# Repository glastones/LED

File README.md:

# LED
LED SPOT (First Try in Kicad)

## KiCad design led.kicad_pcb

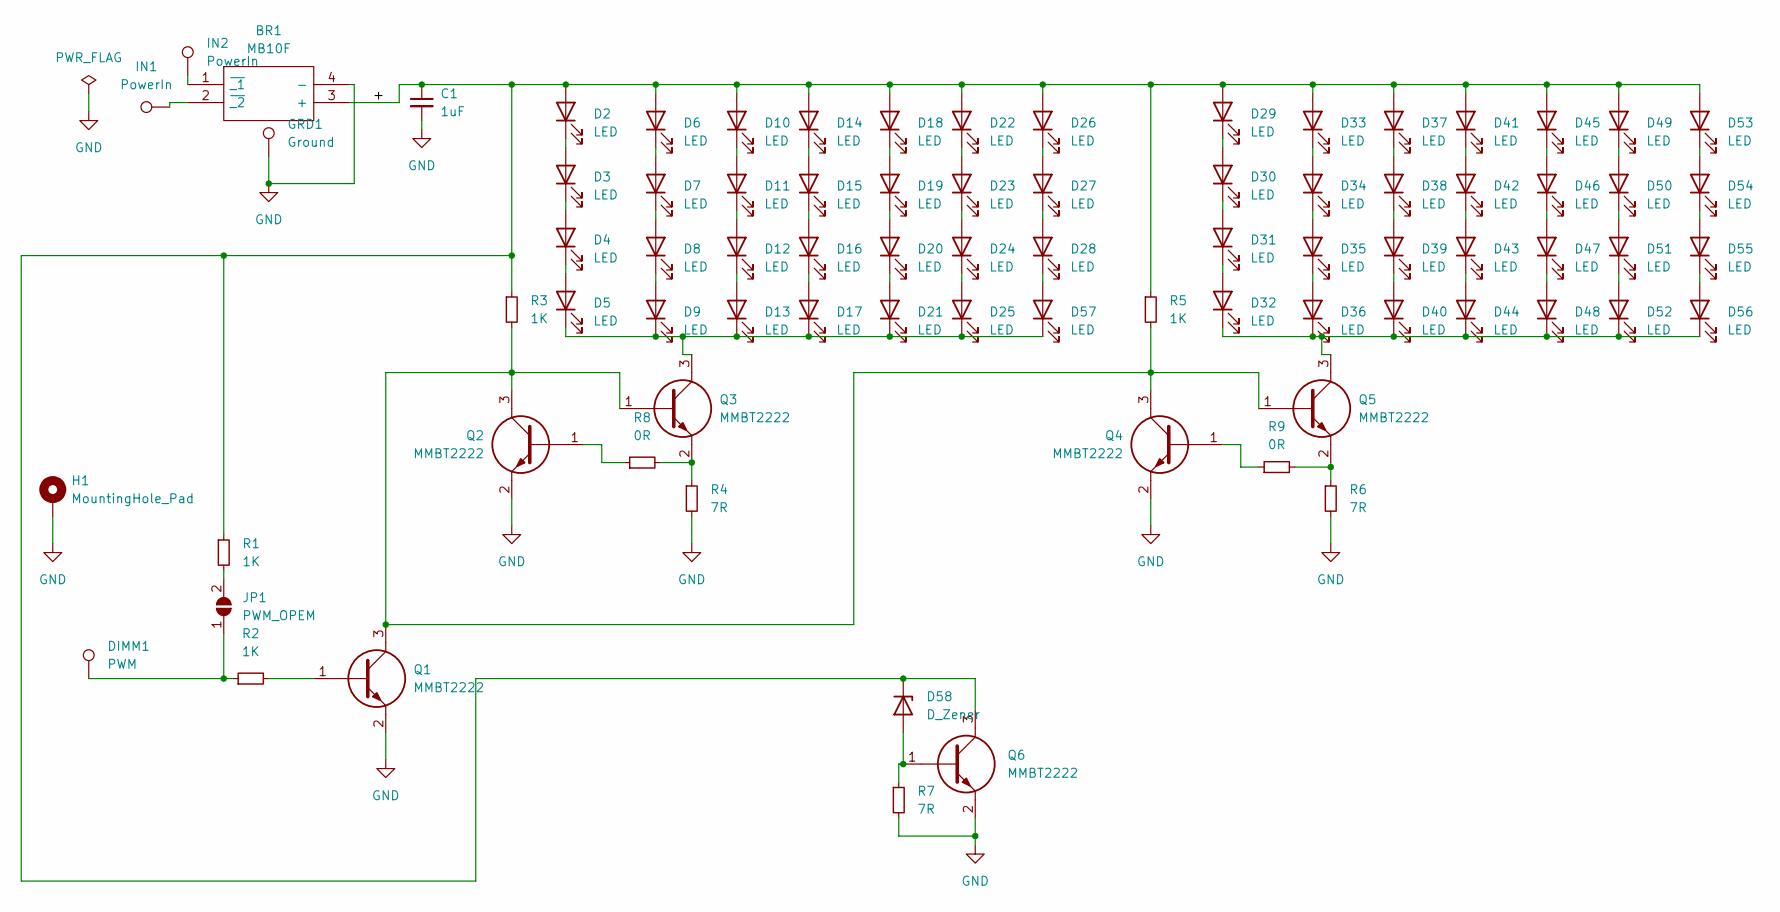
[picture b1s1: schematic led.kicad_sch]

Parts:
BR1: MB10F; SOP250P670X180-4N; Manufacturer_Part_Number MB10F
C1: 1uF; C_0805_2012Metric_Pad1.18x1.45mm_HandSolder
D2, D3, D4, D5, D6, D7, D8, D9, D10, D11, D12, D13, D14, D15, D16, D17, D18, D19, D20, D21, D22, D23, D24, D25, D26, D27, D28, D29, D30, D31, D32, D33, D34, D35, D36, D37, D38, D39, D40, D41, D42, D43, D44, D45, D46, D47, D48, D49, D50, D51, D52, D53, D54, D55, D56, D57: LED; LED_1206_3216Metric_Pad1.42x1.75mm_HandSolder
D58: D_Zener; D_SOD-323_HandSoldering
DIMM1: PWM; TestPoint_Pad_3.0x3.0mm
GRD1: Ground; TestPoint_Pad_D2.0mm
H1: MountingHole_Pad; MountingHole_3.5mm_Pad
IN1, IN2: PowerIn; TestPoint_Pad_3.0x3.0mm
JP1: PWM_OPEM; SolderJumper-2_P1.3mm_Open_Pad1.0x1.5mm
Q1, Q2, Q3, Q4, Q5, Q6: MMBT2222; SOT95P240X114-3N; Manufacturer_Part_Number MMBT2222; Mouser Part Number 512-MMBT2222
R1, R2, R3, R5: 1K; R_0805_2012Metric_Pad1.20x1.40mm_HandSolder
R4, R6, R7: 7R; R_0805_2012Metric_Pad1.20x1.40mm_HandSolder
R8, R9: 0R; R_0805_2012Metric_Pad1.20x1.40mm_HandSolder

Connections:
/+: BR1.3 (+), C1.1, D2.2 (A), D6.2 (A), D10.2 (A), D14.2 (A), D18.2 (A), D22.2 (A), D26.2 (A), D29.2 (A), D33.2 (A), D37.2 (A), D41.2 (A), D45.2 (A), D49.2 (A), D53.2 (A), D58.1 (K), Q6.3, R1.1, R3.1, R5.1
GND: BR1.4 (-), C1.2, GRD1.1, H1.1, Q1.2, Q2.2, Q4.2, Q6.2, R4.2, R6.2, R7.2
unnamed: BR1.1 (~_1), IN2.1
unnamed: BR1.2 (~_2), IN1.1
unnamed: D2.1 (K), D3.2 (A)
unnamed: D3.1 (K), D4.2 (A)
unnamed: D4.1 (K), D5.2 (A)
unnamed: D6.1 (K), D7.2 (A)
unnamed: D7.1 (K), D8.2 (A)
unnamed: D8.1 (K), D9.2 (A)
unnamed: D10.1 (K), D11.2 (A)
unnamed: D11.1 (K), D12.2 (A)
unnamed: D12.1 (K), D13.2 (A)
unnamed: D5.1 (K), D9.1 (K), D13.1 (K), D17.1 (K), D21.1 (K), D25.1 (K), D57.1 (K), Q3.3
unnamed: D14.1 (K), D15.2 (A)
unnamed: D15.1 (K), D16.2 (A)
unnamed: D16.1 (K), D17.2 (A)
unnamed: D18.1 (K), D19.2 (A)
unnamed: D19.1 (K), D20.2 (A)
unnamed: D20.1 (K), D21.2 (A)
unnamed: D22.1 (K), D23.2 (A)
unnamed: D23.1 (K), D24.2 (A)
unnamed: D24.1 (K), D25.2 (A)
unnamed: D26.1 (K), D27.2 (A)
unnamed: D27.1 (K), D28.2 (A)
unnamed: D28.1 (K), D57.2 (A)
unnamed: D29.1 (K), D30.2 (A)
unnamed: D30.1 (K), D31.2 (A)
unnamed: D31.1 (K), D32.2 (A)
unnamed: D32.1 (K), D36.1 (K), D40.1 (K), D44.1 (K), D48.1 (K), D52.1 (K), D56.1 (K), Q5.3
unnamed: D33.1 (K), D34.2 (A)
unnamed: D34.1 (K), D35.2 (A)
unnamed: D35.1 (K), D36.2 (A)
unnamed: D37.1 (K), D38.2 (A)
unnamed: D38.1 (K), D39.2 (A)
unnamed: D39.1 (K), D40.2 (A)
unnamed: D41.1 (K), D42.2 (A)
unnamed: D42.1 (K), D43.2 (A)
unnamed: D43.1 (K), D44.2 (A)
unnamed: D45.1 (K), D46.2 (A)
unnamed: D46.1 (K), D47.2 (A)
unnamed: D47.1 (K), D48.2 (A)
unnamed: D49.1 (K), D50.2 (A)
unnamed: D50.1 (K), D51.2 (A)
unnamed: D51.1 (K), D52.2 (A)
unnamed: D53.1 (K), D54.2 (A)
unnamed: D54.1 (K), D55.2 (A)
unnamed: D55.1 (K), D56.2 (A)
unnamed: D58.2 (A), Q6.1, R7.1
unnamed: DIMM1.1, JP1.1 (A), R2.1
unnamed: JP1.2 (B), R1.2
unnamed: Q1.1, R2.2
unnamed: Q1.3, Q2.3, Q3.1, Q4.3, Q5.1, R3.2, R5.2
unnamed: Q2.1, R8.1
unnamed: Q3.2, R4.1, R8.2
unnamed: Q4.1, R9.1
unnamed: Q5.2, R6.1, R9.2

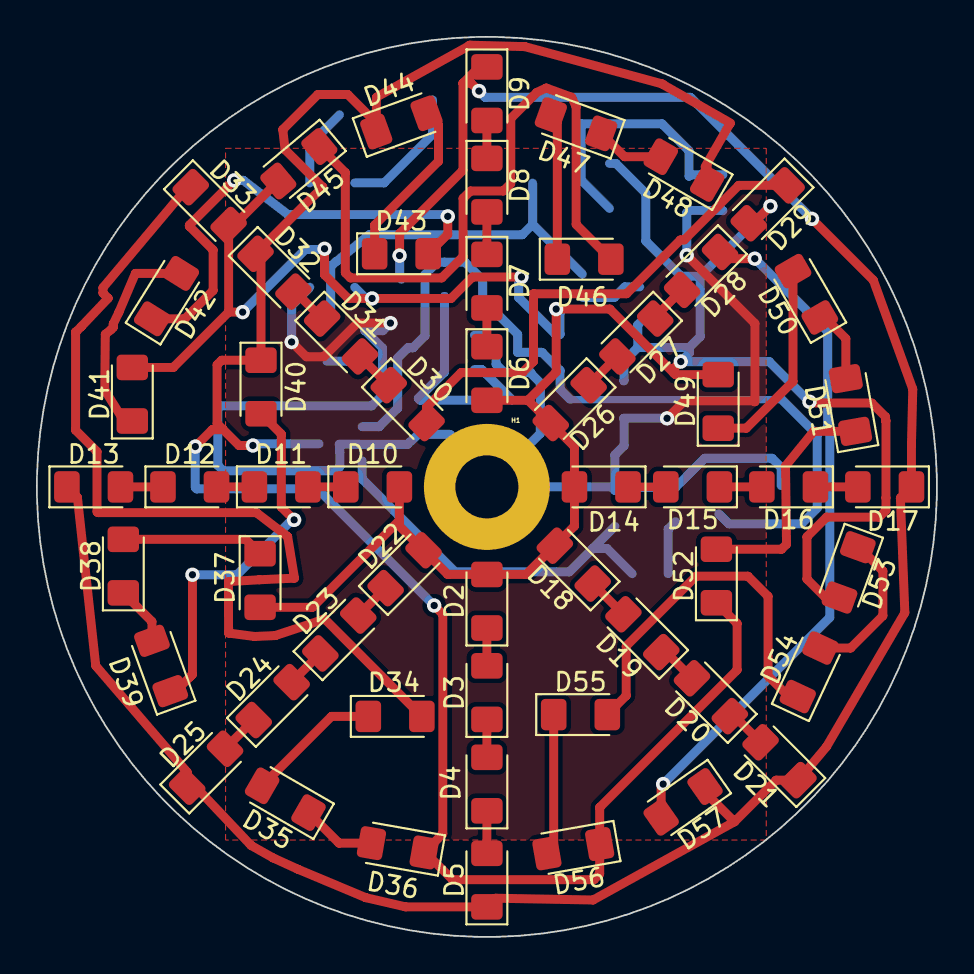
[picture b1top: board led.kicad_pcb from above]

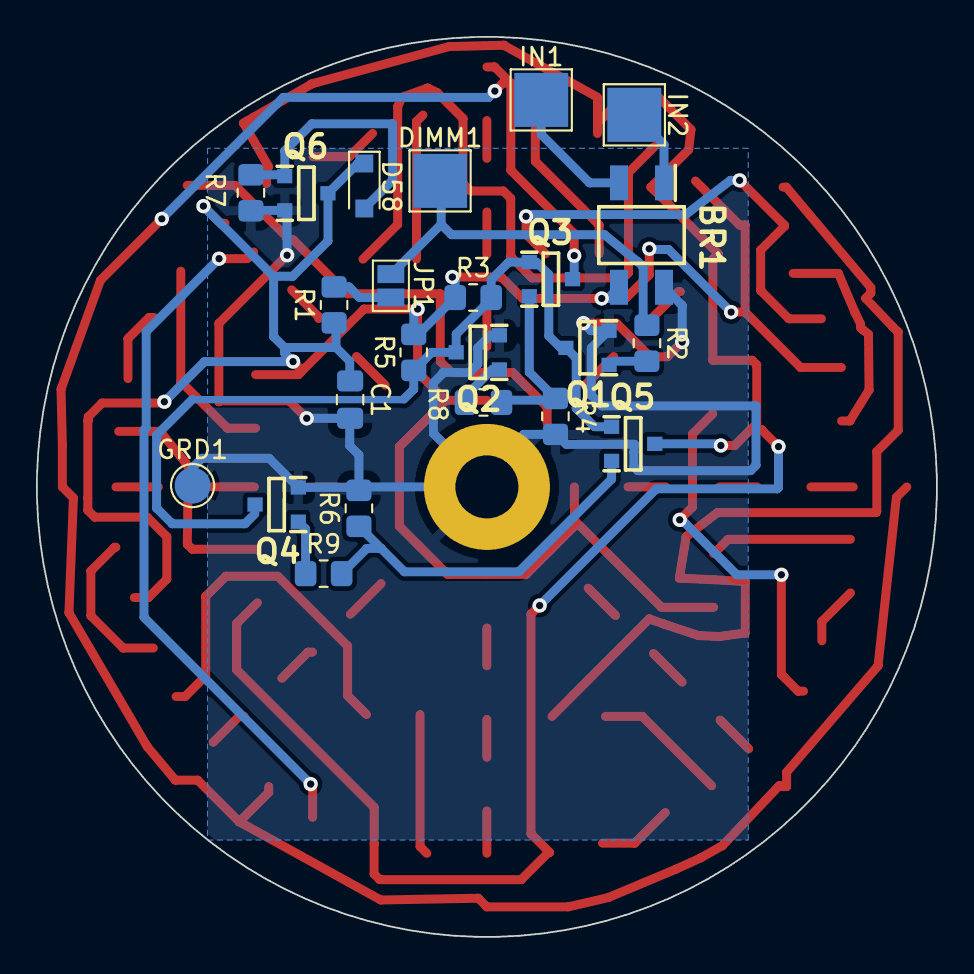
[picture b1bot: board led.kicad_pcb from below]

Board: 2 copper layers, 50.0 x 50.0 mm, 80 parts (23 on the bottom side), 57 nets.

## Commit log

2022-09-30 Add files via upload
    This is a simple led Spot designed in Kicad.
